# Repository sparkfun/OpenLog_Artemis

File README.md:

SparkFun OpenLog Artemis
===========================================================

<table class="table table-hover table-striped table-bordered">
  <tr align="center">
   <td></td>
   <td></td>
  </tr>
  <tr align="center">
    <td><a href="https://www.sparkfun.com/products/16832">SparkFun OpenLog Artemis (DEV-16832)</a></td>
    <td><a href="https://www.sparkfun.com/products/15846">SparkX OpenLog Artemis (SPX-15846)</a></td>
  </tr>
</table>

The OpenLog Artemis is an open source datalogger that comes preprogrammed to automatically log IMU, GPS, serial data, and various pressure, humidity, and distance sensors. All without writing a single line of code! OLA automatically detects, configures, and logs Qwiic sensors. OLA is designed for users who just need to capture a bunch of data to a CSV and get back to their larger project.

Included on every OpenLog Artemis is an IMU for built-in logging of triple axis accelerometer, gyro, and magnetometer. Whereas the original [9DOF Razor](https://www.sparkfun.com/products/14001) used the old MPU-9250, the OpenLog Artemis uses the latest [ICM-20948](https://www.sparkfun.com/products/15335) capable of nearly 1kHz logging of all 9 axis. We then took over a decade of experience with the original [OpenLog](https://www.sparkfun.com/products/13712) and took it much farther. Simply power up OpenLog Artemis and all incoming serial data is automatically recorded to a log file. Baud rates up to 921600bps are supported! Additionally, based on feedback from users we've added an onboard RTC so that all data can be time stamped.

OpenLog Artemis is highly configurable over an easy to use serial interface. Simply plug in a USB C cable and open a terminal at 115200kbps. The logging output is automatically streamed to both the terminal and the microSD. Pressing any key will open the configuration menu.

The OpenLog Artemis automatically scans, detects, configures, and logs various Qwiic sensors plugged into the board (no soldering required!). Currently, auto-detection is supported on the following Qwiic products:

* Any u-blox GPS Modules (Lat/Long, Altitude, Velocity, SIV, Time, Date) such as:
  * [ZED-F9P](https://www.sparkfun.com/products/15136) 1cm High Precision GPS
  * [NEO-M8P-2](https://www.sparkfun.com/products/15005) 2.5cm High Precision GPS
  * [SAM-M8Q](https://www.sparkfun.com/products/15210) 1.5m 72 Channel GPS
  * [ZOE-M8Q](https://www.sparkfun.com/products/15193) 1.5m Compact GPS
  * [NEO-M9N](https://www.sparkfun.com/products/15712) 1.5m GPS
  * [MAX-M10S](https://www.sparkfun.com/products/18037) 1.5m Ultra-Low Power GPS
* [MCP9600 Thermocouple Amplifier](https://www.sparkfun.com/products/16294)
* [NAU7802 Load Cell Amplifier](https://www.sparkfun.com/products/15242)
* [LPS25HB Barometric Pressure Sensor](https://www.sparkfun.com/products/14767)
* [BME280 Humidity and Barometric Pressure Sensor](https://www.sparkfun.com/products/15440)
* [MS5637 Barometric Pressure Sensor](https://www.sparkfun.com/products/14688)
* [MS5837 Depth / Pressure Sensor](https://www.sparkfun.com/products/17709)
* [SDP3X Differential Pressure Sensor](https://www.sparkfun.com/products/17874)
* [MS8607 Pressure Humidity Temperature Sensor](https://www.sparkfun.com/products/16298)
* [MPR0025PA MicroPressure Sensor](https://www.sparkfun.com/products/16476)
* [TMP102 Temperature Sensor] (https://www.sparkfun.com/products/13314)
* [TMP117 High Precision Temperature Sensor](https://www.sparkfun.com/products/15805)
* [AHT20 Humidity and Temperature Sensor](https://www.sparkfun.com/products/16618)
* [SHTC3 Humidity and Temperature Sensor](https://www.sparkfun.com/products/16467)
* [CCS811 Air Quality Sensor](https://www.sparkfun.com/products/14348)
* [SGP30 Air Quality Sensor](https://www.sparkfun.com/products/16531)
* [SGP40 Air Quality Sensor](https://www.sparkfun.com/products/17729)
* [SCD30 CO<sub>2</sub> and Air Quality Sensor](https://www.sparkfun.com/products/15112)
* [SN-GCJA5 Particle Sensor](https://www.sparkfun.com/products/17123)
* [VEML6075 UV Sensor](https://www.sparkfun.com/products/15089)
* [VCNL4040 Proximity Sensor](https://www.sparkfun.com/products/15177)
* [VL53L1X LIDAR Distance Sensor](https://www.sparkfun.com/products/14722)
* [ADS122C04 ADC PT100 Sensor](https://www.sparkfun.com/products/16770)
* [Qwiic Mux](https://www.sparkfun.com/products/16784) allowing for the chaining of up to 64 unique buses!
* [Pulse Oximeter and Heart Rate Sensor](https://www.sparkfun.com/products/15219) (requires exclusive use of pins 32 and 11)
* [ISM330DHCX IMU](https://www.sparkfun.com/products/19764)
* [MMC5983MA Magnetometer](https://www.sparkfun.com/products/19921)
* [KX134 Accelerometer](https://www.sparkfun.com/products/17589)
* [ADS1015 ADC](https://www.sparkfun.com/products/15334)
* [LPS28DFW Barometer](https://www.sparkfun.com/products/21221)
* [VEML7700 Ambient Light Sensor](https://www.sparkfun.com/products/18981)
* [TMP102 Temperature Sensor](https://www.sparkfun.com/sparkfun-digital-temperature-sensor-tmp102-qwiic.html)

Very low power logging is supported. OpenLog Artemis can be configured to take readings at 500 times a second, or as slow as 1 reading every 24 hours. You choose! When there is more than 2 seconds between readings OLA will automatically power down itself and the sensors on the bus resulting in a sleep current of approximately 18uA. This means a normal [2Ah battery](https://www.sparkfun.com/products/13855) will enable logging for more than 4,000 days! OpenLog Artemis has built-in LiPo charging set at 450mA/hr.

New features are constantly being added so we’ve released an easy to use firmware upgrade tool. No need to install Arduino or a bunch of libraries, simply open the [Artemis Firmware Upload GUI](https://github.com/sparkfun/Artemis-Firmware-Upload-GUI), load the latest OLA firmware, and add features to OpenLog Artemis as they come out! Full instructions are available in [UPGRADE.md](UPGRADE.md).

The OLA can be tailored to many different applications and we will be releasing custom versions of the firmware for those too:

* [Latest OLA firmware](https://github.com/sparkfun/OpenLog_Artemis/tree/main/Binaries)
* [Geophone Logger firmware](https://github.com/sparkfun/OpenLog_Artemis_Geophone_Logger) for logging seismic activity
* [GNSS Logger](https://github.com/sparkfun/OpenLog_Artemis_GNSS_Logger) for advanced data logging with the u-blox F9 and M9 GNSS modules including support for RAWX and RELPOSNED

Repository Contents
-------------------

* **/Binaries** - The binary files for the different versions of the OLA firmware.
* **/Firmware** - The main sketch that runs OpenLog Artemis as well as a variety of sketches to test various sensor interfaces and power saving states.
* **/Hardware** - Eagle files.

Documentation
--------------

* **[Hookup Guide](https://learn.sparkfun.com/tutorials/openlog-artemis-hookup-guide)** - hookup guide for the OLA.
* **[UPGRADE.md](./UPGRADE.md)** - contains full instructions on how to upgrade the firmware on the OLA using the [Artemis Firmware Upload GUI](https://github.com/sparkfun/Artemis-Firmware-Upload-GUI).
* **[CONTRIBUTING.md](./CONTRIBUTING.md)** - guidance on how to contribute to this library.
* **[Installing an Arduino Library Guide](https://learn.sparkfun.com/tutorials/installing-an-arduino-library)** - OLA includes a large number of libraries that will need to be installed before compiling will work.
* **[ADDING_SENSORS.md](./ADDING_SENSORS.md)** - contains _abbreviated_ instructions on how to add a new sensor to the OLA firmware. It's more of an aide-memoire really... Sorry about that.
* **[COMPILE_BINARY.md](./COMPILE_BINARY.md)** - contains instructions on how to compile the OLA firmware binary manually using Docker.
* **[SENSOR_UNITS.md](./SENSOR_UNITS.md)** - contains a summary of the units used for each sensor measurement.

Product Versions
----------------
* [DEV-19426](https://www.sparkfun.com/products/19426) - SparkFun OpenLog Artemis without IMU
* [DEV-16832](https://www.sparkfun.com/products/16832) - SparkFun OpenLog Artemis
* [SPX-15846](https://www.sparkfun.com/products/15846) - SparkX OpenLog Artemis

License Information
-------------------

This product is _**open source**_!

Various bits of the code have different licenses applied. Anything SparkFun wrote is beerware; if you see me (or any other SparkFun employee) at the local, and you've found our code helpful, please buy us a round!

Please use, reuse, and modify these files as you see fit. Please maintain attribution to SparkFun Electronics and release anything derivative under the same license.

Distributed as-is; no warranty is given.

- Your friends at SparkFun.

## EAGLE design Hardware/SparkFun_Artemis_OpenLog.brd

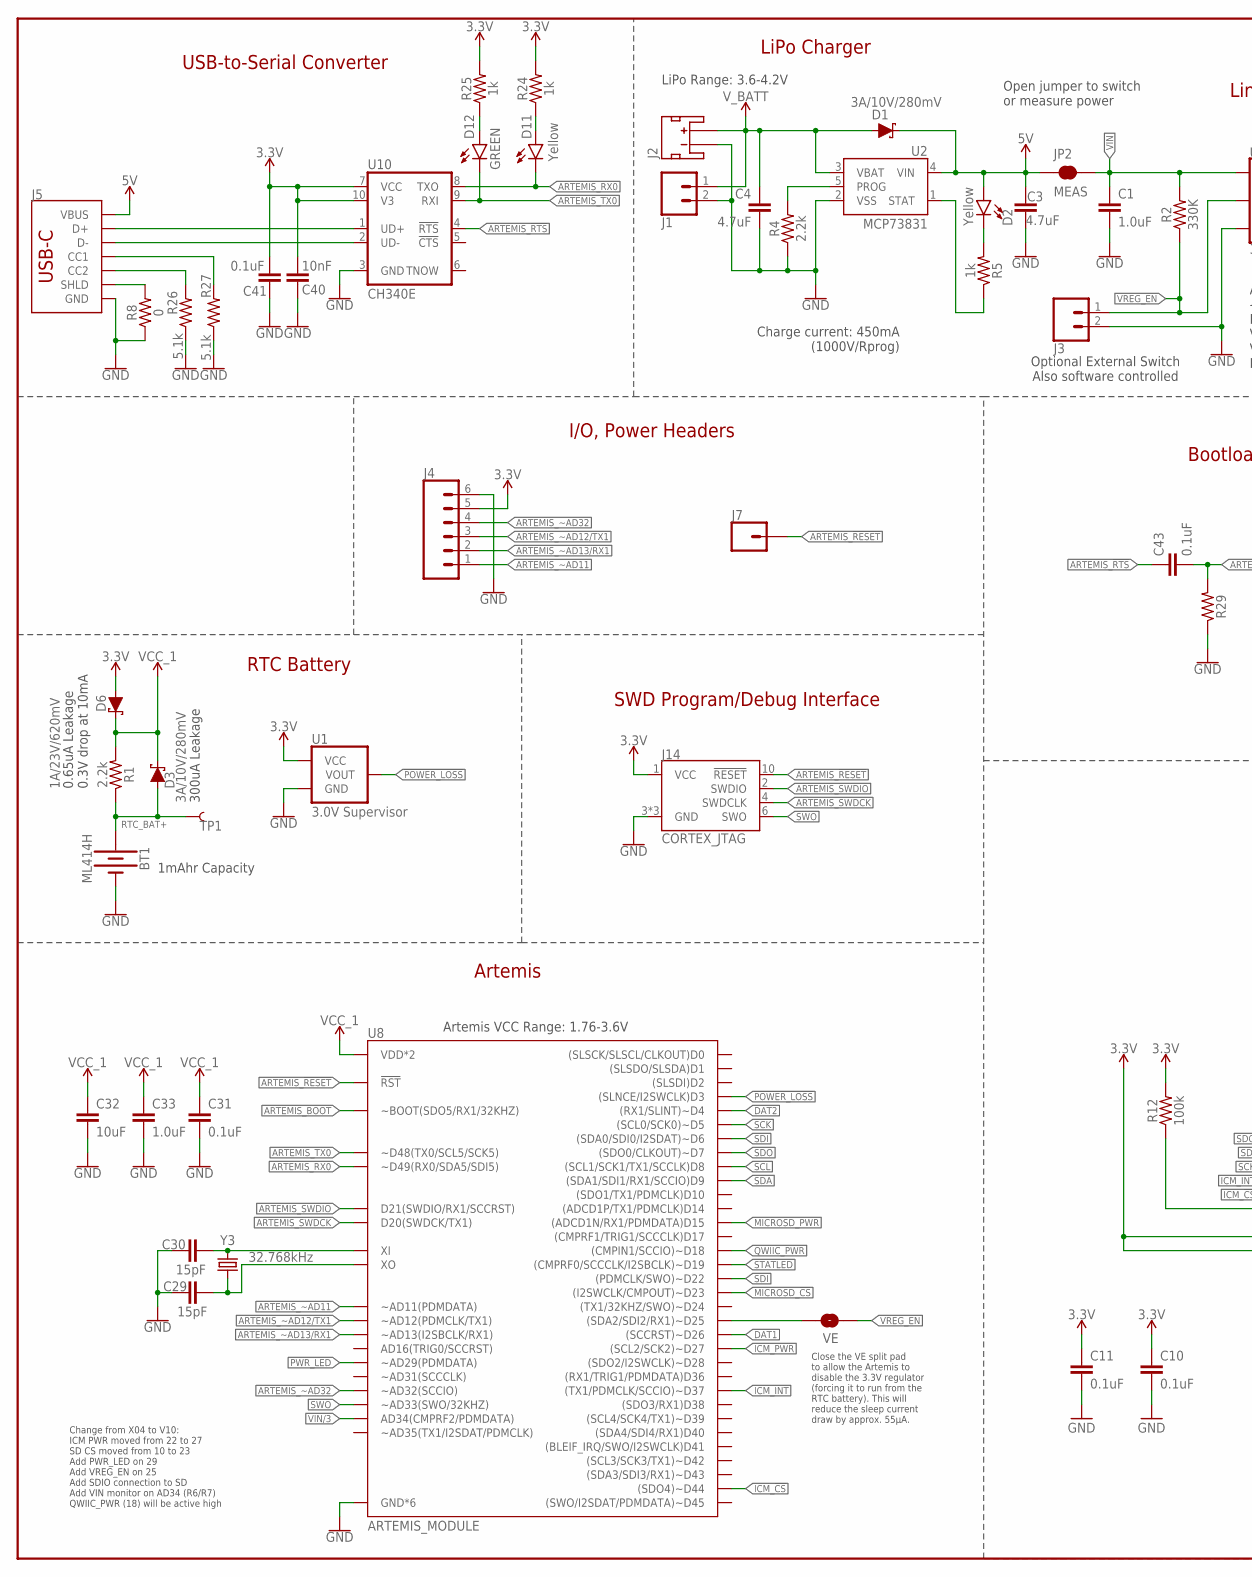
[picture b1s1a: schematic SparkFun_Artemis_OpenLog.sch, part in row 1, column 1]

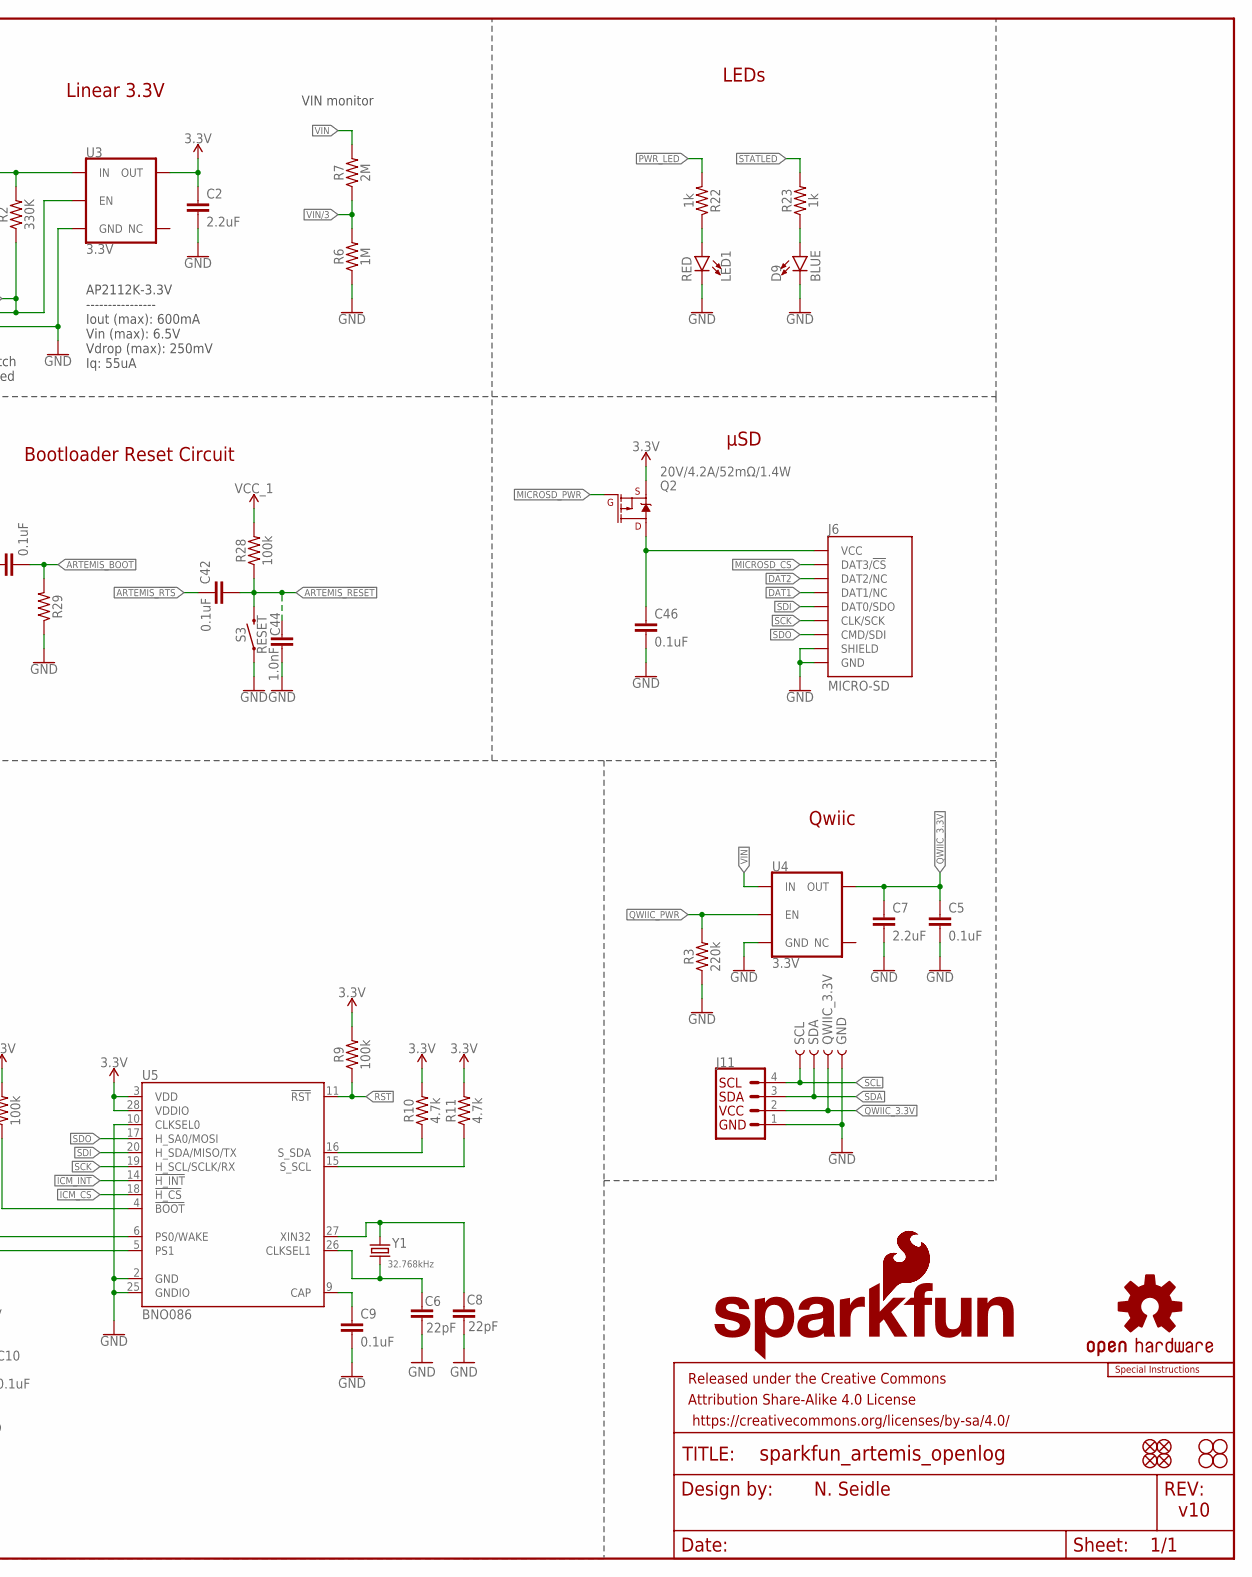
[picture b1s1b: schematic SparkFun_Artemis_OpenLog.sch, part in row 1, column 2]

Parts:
BT1: ML414H; ML414H_IV01E
C1, C33: 1.0uF; 0402-TIGHT
C2, C7: 2.2uF; 0402-TIGHT
C3, C4: 4.7uF; 0402-TIGHT
C5, C31, C41, C42, C43, C46: 0.1uF; 0402-TIGHT
C6, C8: 22pF; 0402-TIGHT
C9, C10, C11: 0.1uF; 0402
C29, C30: 15pF; 0402-TIGHT
C32: 10uF; 0402-TIGHT
C40: 10nF; 0402-TIGHT
C44: 1.0nF; 0402-TIGHT
D1, D3: 3A/10V/280mV; SOD-323
D2, D11: Yellow; LED-0603
D6: 1A/23V/620mV; SOD-323
D9: BLUE; LED-0603
D12: GREEN; LED-0603
FD1, FD2, FD3, FD4: FIDUCIAL1X2; FIDUCIAL-1X2
FRAME1: FRAME-LEDGER; CREATIVE_COMMONS
GND: TEST-POINTTP_15TH_THRU; TP_15TH
H1, H2, H3, H4: STAND-OFF
J1, J3: CONN_021X02_NO_SILK; 1X02_NO_SILK
J2: JST_2MM_MALE; JST-2-SMD
J4: CONN_06NO_SILK_NO_POP; 1X06_NO_SILK
J5: USB_C_4-LAYER_PADS; USB-C-16P_4LAYER-PADS
J6: MICRO-SD; MICRO-SD-SOCKET
J7: CONN_01PTH_NO_SILK_YES_STOP; 1X01_NO_SILK
J11: QWIIC_CONNECTORJS-1MM; JST04_1MM_RA
J14: CORTEX_JTAG; 2X5-PTH-1.27MM
JP2: MEAS; COMBO-JUMPER_2_NC_TRACE
LED1: RED; LED-0603
LOGO1: SFE_LOGO_NAME.1_INCH; SFE_LOGO_NAME_.1
LOGO2: OSHW-LOGOS; OSHW-LOGO-S
LOGO3: SPECIAL_INSTRUCTIONS-ORDERING; ORDERING_INSTRUCTIONS
LOGO4, LOGO5: SFE_LOGO_FLAME.1_INCH; SFE_LOGO_FLAME_.1
Q2: 20V/4.2A/52mΩ/1.4W; SOT23-3
QWIIC_3.3V: TEST-POINTTP_15TH_THRU; TP_15TH
R1, R4: 2.2k; 0402-TIGHT
R2: 330K; 0402-TIGHT
R3: 220k; 0402-TIGHT
R5, R22, R23, R24, R25: 1k; 0402-TIGHT
R6: 1M; 0402-TIGHT
R7: 2M; 0402-TIGHT
R8: 0; 0402-TIGHT
R9, R12, R28: 100k; 0402-TIGHT
R10, R11: 4.7k; 0402-TIGHT
R26, R27: 5.1k; 0402-TIGHT
R29: 220KOHM-0402T-1/16W-1%; 0402-TIGHT
S3: RESET; TACTILE_SWITCH_SMD_4.6X2.8MM
SCL: TEST-POINTTP_15TH_THRU; TP_15TH
SDA: TEST-POINTTP_15TH_THRU; TP_15TH
TP1: TEST-POINT3; PAD.03X.03
U1: 3.0V Supervisor; SOT23-3
U2: MCP73831; SOT23-5
U3, U4: 3.3V; SOT23-5
U5: BNO086; LGA-28
U8: ARTEMIS_MODULE; ARTEMIS_FP
U10: CH340E; MSOP10
VE: JUMPER-SMT_2_NO_SILK; SMT-JUMPER_2_NO_SILK
Y1, Y3: 32.768kHz; CRYSTAL-SMD-3.2X1.5MM

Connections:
3.3V: C2.1, C10.1, C11.1, C40.1, C41.1, D6.A, J4.5, J14.1 (VCC), Q2.2 (S), R9.2, R10.2, R11.2, R12.2, R24.2, R25.2, U1.3 (VCC), U3.5 (OUT), U5.3 (VDD), U5.5 (PS1), U5.6 (PS0/WAKE), U5.28 (VDDIO), U10.7 (VCC), U10.10 (V3)
5V: C3.1, D1.C, D2.A, J5.VBUS1 (VBUS), J5.VBUS2 (VBUS), JP2.1, JP2.3 (1), U2.4 (VIN)
!POWER_LOSS!: U1.2 (VOUT), U8.D3 ((SLNCE/I2SWCLK)D3)
!RST: R9.1, U5.11 (!RST)
ARTEMIS_!RESET: C42.2, C44.1, J7.1, J14.10 (!RESET), R28.1, S3.3 (2), S3.4 (2), U8.~RST (!RST)
ARTEMIS_!RTS!: C42.1, C43.1, U10.4 (!RTS)
ARTEMIS_BOOT: C43.2, R29.2, U8.BOOT (~BOOT(SDO5/RX1/32KHZ))
ARTEMIS_RX0: D11.C, U8.RXI-0 (~D49(RX0/SDA5/SDI5)), U10.8 (TXO)
ARTEMIS_SWDCK: J14.4 (SWDCLK), U8.SWDCK (D20(SWDCK/TX1))
ARTEMIS_SWDIO: J14.2 (SWDIO), U8.SWDIO (D21(SWDIO/RX1/SCCRST))
ARTEMIS_TX0: D12.C, U8.TXO-0 (~D48(TX0/SCL5/SCK5)), U10.9 (RXI)
ARTEMIS_~AD11: J4.1, U8.~AD11 (~AD11(PDMDATA))
ARTEMIS_~AD12/TX1: J4.3, U8.~AD12 (~AD12(PDMCLK/TX1))
ARTEMIS_~AD13/RX1: J4.2, U8.~AD13 (~AD13(I2SBCLK/RX1))
ARTEMIS_~AD32: J4.4, U8.~AD32 (~AD32(SCCIO))
CC3: J5.B5 (CC2), R26.2
CC4: J5.A5 (CC1), R27.2
CHG_LED: R5.1, U2.1 (STAT)
D+2: J5.A6 (D+), J5.B6 (D+), U10.1 (UD+)
D-2: J5.A7 (D-), J5.B7 (D-), U10.2 (UD-)
DAT1: J6.DAT1 (DAT1/NC), U8.~D26 ((SCCRST)~D26)
DAT2: J6.DAT2 (DAT2/NC), U8.~D4 ((RX1/SLINT)~D4)
GND: BT1.-, C1.2, C2.2, C3.2, C4.2, C5.2, C6.2, C7.2, C8.2, C9.2, C10.2, C11.2, C29.1, C30.1, C31.1, C32.2, C33.2, C40.2, C41.2, C44.2, C46.2, D9.C, GND.P$1, J1.2, J2.1 (-), J3.2, J4.6, J5.GND, J5.GND2 (GND), J6.CD1 (SHIELD), J6.GND, J6.GND1 (GND), J6.GND3 (GND), J11.1, J14.3 (GND), J14.5 (GND), J14.9 (GND), LED1.C, R3.1, R4.1, R6.1, R8.1, R26.1, R27.1, R29.1, S3.1, S3.2 (1), U1.1 (GND), U2.2 (VSS), U3.2 (GND), U4.2 (GND), U5.2 (GND), U5.10 (CLKSEL0), U5.25 (GNDIO), U8.GND@1 (GND*6), U8.GND@22 (GND*6), U8.GND@38 (GND*6), U8.GND@39 (GND*6), U8.GND@47 (GND*6), U8.GND@59 (GND*6), U10.3 (GND)
ICM_!CS!: U5.18 (!H_CS), U8.~D44 ((SDO4)~D44)
ICM_INT: U5.14 (!H_INT), U8.~D37 ((TX1/PDMCLK/SCCIO)~D37)
ICM_PWR: U8.~D27 ((SCL2/SCK2)~D27)
MICROSD_!CS!: J6.CS/DAT3 (DAT3/!CS!), U8.~D23 ((I2SWCLK/CMPOUT)~D23)
MICROSD_PWR: Q2.1 (G), U8.D15 ((ADCD1N/RX1/PDMDATA)D15)
unnamed: J5.SHLD1 (SHLD), J5.SHLD2 (SHLD), J5.SHLD3 (SHLD), J5.SHLD4 (SHLD), R8.2
unnamed: C8.1, U5.27 (XIN32), Y1.P$2 (2)
unnamed: C6.1, U5.26 (CLKSEL1), Y1.P$1 (1)
unnamed: C9.1, U5.9 (CAP)
unnamed: R12.1, U5.4 (!BOOT)
unnamed: R4.2, U2.5 (PROG)
unnamed: D2.C, R5.2
unnamed: C29.2, U8.XO, Y3.P$2 (2)
unnamed: C30.2, U8.XI, Y3.P$1 (1)
unnamed: LED1.A, R22.1
unnamed: D9.A, R23.1
unnamed: D12.A, R25.1
unnamed: D11.A, R24.1
PWR_LED: R22.2, U8.~AD29 (~AD29(PDMDATA))
QWIIC_3.3V: C5.1, C7.1, J11.2, QWIIC_3.3V.P$1, U4.5 (OUT)
QWIIC_PWR: R3.2, U4.3 (EN), U8.~D18 ((CMPIN1/SCCIO)~D18)
RTC_BAT+: BT1.+, D3.A, R1.1, TP1.P$1
SCK: J6.SCLK (CLK/SCK), U5.19 (H_SCL/SCLK/RX), U8.~D5 ((SCL0/SCK0)~D5)
SCL: J11.4, SCL.P$1, U8.D8 ((SCL1/SCK1/TX1/SCCLK)D8)
SDA: J11.3, SDA.P$1, U8.D9 ((SDA1/SDI1/RX1/SCCIO)D9)
SDI: J6.DO/DAT0 (DAT0/SDO), U5.20 (H_SDA/MISO/TX), U8.~D6 ((SDA0/SDI0/I2SDAT)~D6), U8.~D22 ((PDMCLK/SWO)~D22)
SDO: J6.DI/CMD (CMD/SDI), U5.17 (H_SA0/MOSI), U8.D7 ((SDO0/CLKOUT)~D7)
SD_PWR: C46.1, J6.VCC, Q2.3 (D)
STATLED: R23.2, U8.~D19 ((CMPRF0/SCCCLK/I2SBCLK)~D19)
SWO: J14.6 (SWO), U8.~AD33/SWO (~AD33(SWO/32KHZ))
S_SCL: R11.1, U5.15 (S_SCL)
S_SDA: R10.1, U5.16 (S_SDA)
VCC_1: C31.2, C32.1, C33.1, D3.C, D6.C, R1.2, R28.2, U8.VDD@36 (VDD*2), U8.VDD@37 (VDD*2)
VIN: C1.1, JP2.2, JP2.4 (2), R2.2, R7.2, U3.1 (IN), U4.1 (IN)
VIN/3: R6.2, R7.1, U8.AD34 (AD34(CMPRF2/PDMDATA))
VREG_EN: J3.1, R2.1, U3.3 (EN), VE.2
VREG_EN1: U8.~D25 ((SDA2/SDI2/RX1)~D25), VE.1
V_BATT: C4.1, D1.A, J1.1, J2.2 (+), U2.3 (VBAT)

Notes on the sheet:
AP2112K-3.3V ---------------- Iout (max): 600mA Vin (max): 6.5V Vdrop (max): 250mV Iq: 55uA
v10
N. Seidle
LiPo Charger
I/O, Power Headers
LiPo Range: 3.6-4.2V
Charge current: 450mA (1000V/Rprog)
SWD Program/Debug Interface
Artemis
Artemis VCC Range: 1.76-3.6V
Linear 3.3V
Open jumper to switch or measure power
USB-to-Serial Converter
Bootloader Reset Circuit
μSD
Qwiic
RTC Battery
Optional External Switch Also software controlled
300uA Leakage
0.65uA Leakage 0.3V drop at 10mA
1mAhr Capacity
Change from X04 to V10: ICM PWR moved from 22 to 27 SD CS moved from 10 to 23 Add PWR_LED on 29 Add VREG_EN on 25 Add SDIO connection to SD Add VIN monitor on AD34 (R6/R7) QWIIC_PWR (18) will be active high
VIN monitor
LEDs
Close the VE split pad to allow the Artemis to disable the 3.3V regulator (forcing it to run from the RTC battery). This will reduce the sleep current draw by approx. 55μA.

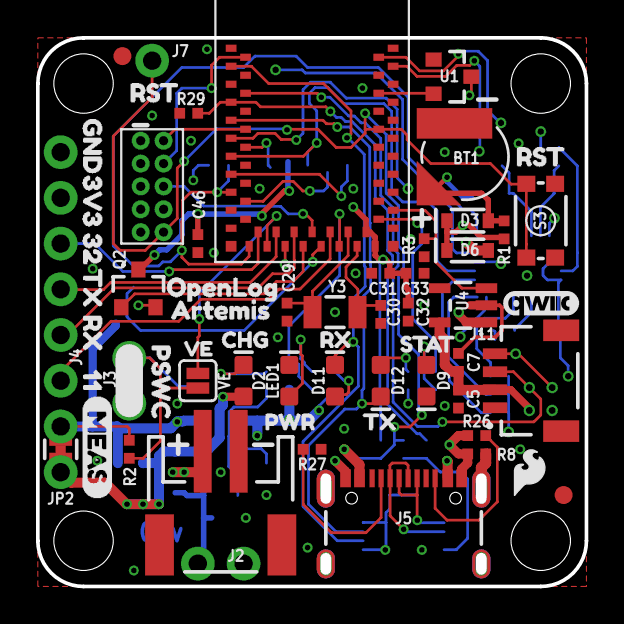
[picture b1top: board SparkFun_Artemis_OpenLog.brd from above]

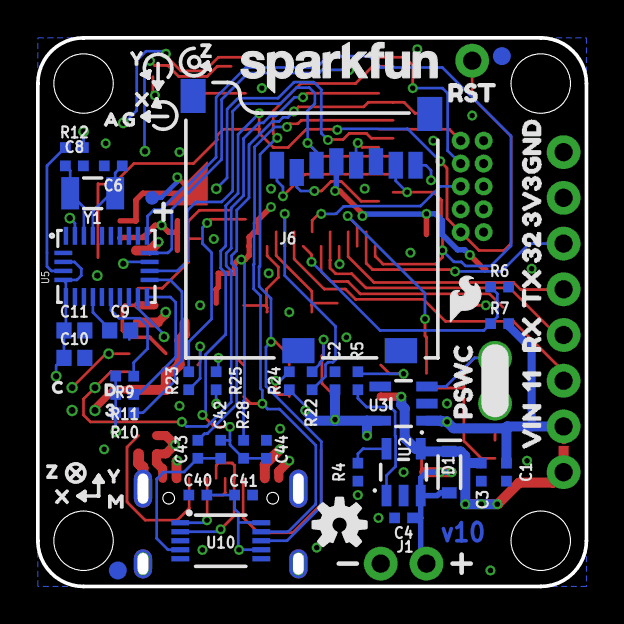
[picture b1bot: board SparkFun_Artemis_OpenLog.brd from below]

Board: 4 copper layers, 30.5 x 30.5 mm, 132 parts (66 on the bottom side), 60 nets.

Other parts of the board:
U$1: QWIIC#LOGO#JPG
U$2: CHG2
U$3: PWR0
U$4: RX4
U$5: STAT5
U$6: VE0
U$7: TX3
U$8, U$12: RST0
U$9: ARTEMIS13
U$10, U$11: PSWC0
U$13: C0
U$14: D0
U$15: 30
U$27: MEAS3
U$28: OPENLOG12
U$32: RST9
U$33: VIN8
U$34, U$35: 3V34
U$36, U$37: 113
U$38, U$39: 322
U$40, U$41: GND5
U$42, U$54: RX1
U$43, U$49: X0
U$44, U$50: Y1
U$45, U$51: Z2
U$46: G5
U$47: A4
U$48: M3
U$55, U$56: TX0

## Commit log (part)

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2020-06-29 V10 PCB tweaks following design review
2020-06-29 Added revised production files (3x5)
2020-06-30 Final V10 PCB tweaks!?
2020-06-30 Corrections and new features for #18
2020-07-04 Added support for the ADS122C04 ADC (Qwiic PT100)
2020-07-14 Reverting to standard SdFat. Removed the wakeOnPowerReconnect & WDT functionality.
2020-07-18 Added the olaIdentifier and corrected the qwiic pull-ups.
    Pull-ups are now only disabled when talking to a u-blox GNSS.
2020-07-18 Removed the last of the msg
2020-07-20 Added qwiicBusPullUps to the settings
2020-07-20 Removing the v14 BETA binaries
2020-07-22 Increase port count to 8 on mux scanner
2020-08-01 Work in progress:
    Added the skeleton of the productionTest however some parts are about to go in the bin as I've just found out that the Apollo3 does not support I2C peripheral mode!
2020-08-01 productionTest now uses the TX and RX pins
2020-08-03 Added the microSD card test
2020-08-03 Changed max serial logging baud rate to 500000.
    Tested serial logging at 460800 and 921600 using u-blox serial data. 460800 works fine but 921600 causes problems... To play safe, I'm limiting the maximum serial logging baud rate to 500000.
2020-08-04 Fixing the slippery mux bug
2020-08-05 Reduce RAM use by making all Serial prints F
2020-08-06 Added EXTRA_MUX_STARTUP_BYTES
2020-08-10 Make I2C scanner work on new v10 hardware. Add delay for devices, ublox needs ~1s to ack.
2020-08-10 Move Qwiic power up delay from startup to detectQwiicDevices()
2020-08-10 Remove erroneous print warning
2020-08-10 Add record length to debug print
2020-08-11 Making board and sch consistant.
2020-08-13 Move up initial power on of Qwiic bus.
    There are a few configurations (no SD card, fast SD card with few files) where OLA powers up the GPS module but fails to detect it because the GPS module needs more time (around 1s) after power on. T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
2020-08-13 Change firmware number
2020-08-13 Whitespace changes - Arduino autoformat
2020-08-13 Add power down before power on for SCD30 test
2020-08-21 Update readme with v10 red OLA
2020-08-21 Update auto-detect list
2020-08-22 Removed duplicated text in README.md
2020-09-01 Added support to output sensor data to the TX pin
2020-09-03 Added file create and access timestamps
2020-09-03 Added measurementTotal
2020-09-04 Added the Tera Term change directory message
2020-09-04 Added qwiic bus power up delays for each sensor type
    Each sensor struct now contains a powerOnDelayMillis.
    qwiicPowerOnDelayMillis is set to the _higher_ of settings.qwiicBusPowerUpDelayMs or the highest power on delay depending on what sensors are attached.
    The minimum value for settings.qwiicBusPowerUpDelayMs is minimumQwiicPowerOnDelay.
2020-09-07 Added frequent log file access timestamps
2020-09-07 Added the ability to trigger a sensor reading via pin 11
2020-09-07 Updated the power-on delay for the SCD30
2020-09-07 Updated the (done) list for v16
2020-09-07 Added the binaries for v16
2020-09-16 Added a fix for issue #39
2020-10-08 Restructuring detectQwiicDevices so that the MCP9600 is detected correctly
2020-10-08 Updating the v17_BETA binary. Now supports the MCP9600.
2020-10-12 Adding support for the MPR MicroPressure and SN-GCJA5 Particle sensors
2020-10-13 Added ADDING_SENSORS.md
2020-10-13 Updated the CHANGELOG and binaries for v1.7
2020-10-14 Updated SENSOR_UNITS.md
2020-10-15 DOP is dimensionless. Who knew!?
2020-11-27 Add logMicroseconds
2020-11-30 Adding support for the BNO080 - ** work in progress ** (does not .begin reliably)
2020-12-01 Revert "Adding support for the BNO080 - ** work in progress ** (does not .begin reliably)"
    This reverts commit cdaf6afa03d717202459b980fb657dd0dfe09e62.
2020-12-06 Changing the sprintf for micros() from %d to %lu
2020-12-06 Adding v19 BETA
2020-12-06 Correcting the magnetometer typo
2021-01-04 goToSleep() is now called with argument
    The goToSleep function is now called with an argument msToSleep so it can be used either when sleeping between samples, or for a potentially much longer sleep when triggered on an external pin.
2021-01-06 Changed minimum Deep Sleep time to global constant
2021-01-06 Added timestamping to Serial data after a newline
2021-01-28 cleanup
2021-01-29 Adding the timestamp feature as described in PR #70 and Issue #63. Deleted settings.getRTCfromGPS
2021-01-29 Adding "sleep on pin" and "wake at specified time" functionality
    These changes are based on code by @ryanneve in PR #64 and suggestions in Issue #46
2021-01-30 Correcting logHertz. Slow logging start and end times now entered as hour and minute - not minute-of-day.
2021-01-30 Adjust msToSleep if checkSleepOnRTCTime is true and we need to wake before slowLoggingIntervalSeconds * 1000
2021-01-30 Update OpenLog_Artemis-V10-v19_BETA.bin
    v1.9 BETA now includes msToSleep adjustment for the RTC case
2021-02-01 Try to stagger SCD30 readings to stagger the peak current draw
2021-02-02 Adding resetOnZeroDeviceCount
2021-02-02 Re-adding BNO080
2021-02-02 Adding SGP40, SDP3X and MS5837
2021-02-05 Improvements for the MS5837
2021-02-28 Adding IMU DMP examples
2021-03-09 SDP3X corrections - need to use continuous measurements
2021-03-09 Adding stopContinuousMeasurement for the SDP3X
2021-03-10 SDP3X: add 1ms delay between stopContinuousMeasurement and startContinuousMeasurement
2021-03-30 Correct issue #79
2021-03-30 Update low-power code as per #78
2021-03-30 Update DMP examples
2021-04-23 Correct Issue #82
2021-04-26 Add IMU DMP Multiple Sensors example - requires v1.2.5 of the ICM20948 library
2021-04-26 Initial commit with DMP support
2021-05-28 Add support for exFAT. Requires v2.0.6 of Bill Greiman's SdFat library
2021-05-28 Add minimumAwakeTimeMillis : #83
2021-05-28 minimumAwakeTimeMillis improvements. Fix an old bug in msBeenAwake
2021-05-30 Update to Apollo3 v2.1.0 - work in progress
2021-05-31 Adding oximeter MODE_TWO support
2021-06-01 Update GNSS_Data_Logging.ino - add exFAT support (SdFat v2.0.6)
2021-06-04 Add printf support
2021-06-18 Debugging sleep functionality
2021-07-05 Increase DMP data to five decimal places
2021-07-05 Add v1.12 BETA binary
2021-07-07 Fix goToSleep. Increase DMP resolution. Add bestMillis(). Add comma after olaftoa values.
    With v2.1 of the core, both millis and micros are corrupted when coming out of deep sleep. bestMillis will use the RTC to generate the milliseconds.
2021-07-08 Add configureSerial1TxRx. Improvements to the sleep current - disable SPI and qwiic pins.
2021-07-09 Add printGNSSDebugMessages and gnssFactoryDefault
2021-07-15 Corrections for Qwiic bus speed (100kHz and 400kHz). Ensure interrupt directions are set correctly.
2021-07-16 v2.0
2021-08-17 Update test sketches for v2.1 of Apollo3
2021-08-17 Update AutoDetectWithMux - add ICM20948
2021-09-11 Simplify SD_FAT_TYPE type switching
2021-09-11 Update gitignore
2021-12-14 Add BME280 test to correct issue #109
2021-12-14 Update change notes
2022-03-31 Add support for yyyy/mm/dd and ISO 8601 date. Add fix for Serial.end.
    Add support for missing / not-populated IMU.
    Note: we're not out of the woods yet... The IMU is not restarting after sleep. More changes to follow!
2022-03-31 Add support for fractional time zone offsets
2022-04-01 Use rtcMillis everywhere
2022-04-07 Correct ublox spelling. Update production test. Add X04 BETA binary.
2022-04-08 Release firmware 2.2
2022-05-02 Update OpenLog_Artemis.ino
    Only go into menu on character ASCII value >= 11. Prevents menu if qwiic powered BLE module generates noise on power-up.
2022-08-01 v1.2.3
2022-08-01 v2.3
2022-08-16 Add NoPowerLossProtection option and binary
2022-08-18 minor refactor of header output logic, added header output token for serial output, removed print of header to serial on file change, moved strcat to strlcat
2022-08-26 Add settings.openMenuWithPrintable - accessible from the "d" debug menu
2022-09-06 Update README.md
    Request by a customer to add the recently released MAX-M10S to the list of GNSS modules. I also updated the wording to indicate that the OpenLog Artemis can be linked to any of the u-blox modules.
    No need to update the version number of this repo since it's just the README.md .
2022-12-02 Add support for BMP390 on 0x77
2022-12-05 Set sampling mode to normal precision
2022-12-05 Fix mistakes preventing compiling and adding readme files
2023-01-10 Adds SD card menu timeout (60 sec)
2023-01-10 Re-use same datafile after entering SD card menu unless deleted
2023-01-12 Add debug menu set options for nextDataLogNumber and nextSerialLogNumber
2023-01-12 Correct MMC5983 scaling
2023-01-13 Undo log file reset feature
2023-01-13 ISM330 improvements
2023-01-13 Resolve #87
2023-01-13 Update version comments
2023-01-18 Update 2.5 binaries - correct KX134 functionality
2023-01-23 Add support for ICM20948 via I2C
    Acceleration, Gyro, Mag and Temp supported.
2023-02-06 Only disable I2C SDA and SCL during sleep when I2C bus is being powered down.
2023-02-28 Add input buffer flush on wakeup from sleep
2023-03-28 Added scripts to build using arduino-cli.
2023-03-28 add support for INA3221, MCP23017 and MAX11615
2023-08-29 add a dockerfile for compiling the firmware
2023-08-30 install unzip at start
2023-08-30 don't install unnecessary packages
2023-08-30 Add LPS28DFW library
2023-09-14 docker: cache build
2023-09-18 downgrade sdfat to 2.2.0
2023-10-25 Added SCD30 FRC calibration to config menu
2023-10-25 Corrected original ICM20948 path, whitespace
2024-02-21 Add missing quote
2024-02-21 Enable DMP with sed
2024-02-21 Pushing new firmware binary
2024-02-21 Tidy up after #179
2024-02-21 Update comments
2024-02-21 Allow negative weights on NAU7802
2024-02-22 Fix nvm calibrationWeight
2024-02-22 NAU7802 improvements - skip calibrateAFE on begin
2024-02-24 Better NAU7802 support - needs v1.0.5 of the NAU7802 library
2024-02-26 Change zeroOffset type
2024-02-26 Fix minor bug : pass correct array size to olaftoa
2024-02-26 Fix major bug : configure Mux when changing settings of NAU7802, SCD30 or u-blox GNSS
2024-03-04 2.7 BETA
2024-03-07 v2.8 BETA - to resolve #192
2024-03-07 v2.8 BETA
2024-08-09 Update version notes
2024-09-13 Adding TMP102 library link to documentation as a required library.
2024-09-14 Updated documentation to reflect the new package path name.
2024-09-22 Added support for differentating between the ADS1015 ADC chip vs the TMP102 temperature sensor based upon the R0/R1 configuration bits in the TMP102 which are locked read only to 11, while the same b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
2024-11-08 Revert SparkFun_ICM-20948_ArduinoLibrary vs SparkFun_ICM-20948_ArduinoLibrary
2024-11-08 Moving "(done)" comment to bottom of list
2024-11-11 Add TMP102 to build actions
2025-02-03 actions/upload-artifact@v4
2025-02-06 Where possible, write residual serial data to file before closing
2025-02-06 Don't delete OLA_ settings.txt
2025-02-06 Update sdCardHelp
2025-09-17 Add Mode 1/2 option for LPS28DFW sensor with SD card persistence
2025-11-07 Move LPS28DFW setModeConfig into configureDevice
2025-11-07 v2.11
2025-11-07 Update Dockerfile - comment power loss protection and X04 build

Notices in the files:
parts and their libraries:
SparkFun-Capacitors: Licensing: Creative Commons ShareAlike 4.0 International - https://creativecommons.org/licenses/by-sa/4.0
SparkFun-Aesthetics: Released under the Creative Commons Attribution Share-Alike 4.0 License
SparkFun-Aesthetics: https://creativecommons.org/licenses/by-sa/4.0
